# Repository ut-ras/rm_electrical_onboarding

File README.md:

# RoboMaster Electrical Onboarding Project
This repository contains the _onboarding project_ for UT RoboMasters. For the full electrical team onboarding process, see [the main repository's wiki page](https://github.com/ut-ras/robomaster_electrical/wiki/New-Members#onboarding). 
## Overview
This project will take you through the full PCB design process of a boost converter circuit alongside a simple data connection standard. The design process is as follows:

1. Characterization:
   * Defining what the board should do and what problems it needs to solve
2. Schematic creation:
   * Clearly defining circuits and connections without the clutter of physical implementation
   * Running DRC to catch definition errors before they break our board layout
3. Simulation:
   * Simulating the circuits defined in the schematic to verify our intentions
4. Board Layout & Routing:
   * Determining an optimal arrangement for components and routing connections, the physical implementation
   * Running DRC to verify our implementation is manufacturable and repeating anything in steps 2-4 to resolve issues
6. File Export:
   * Generating gerber files that manufacturers can use to produce the board design

This is an **involved process** and will likely take 3-4 hours, but please put some real time and effort in as you will need every skill you develop here.\
Get started by seeing [the wiki](https://github.com/ut-ras/rm_electrical_onboarding/wiki) for this repo.\
**PLEASE** ask questions in the Onboarding Discussion thread on the Discord, someone else likely has the same question!

## Next Steps

TODO: add up-to-date wiring diagram
Once you're done and are looking to see what you'll be applying your skills to, check out [the problem statement presentation](https://github.com/ut-ras/rm_electrical-supercap_v2/blob/main/UT%20Robomasters%20%E2%80%93%20Supercap%20System%20Overview.pptx) for [supercap](https://github.com/ut-ras/rm_electrical-supercap_v2).

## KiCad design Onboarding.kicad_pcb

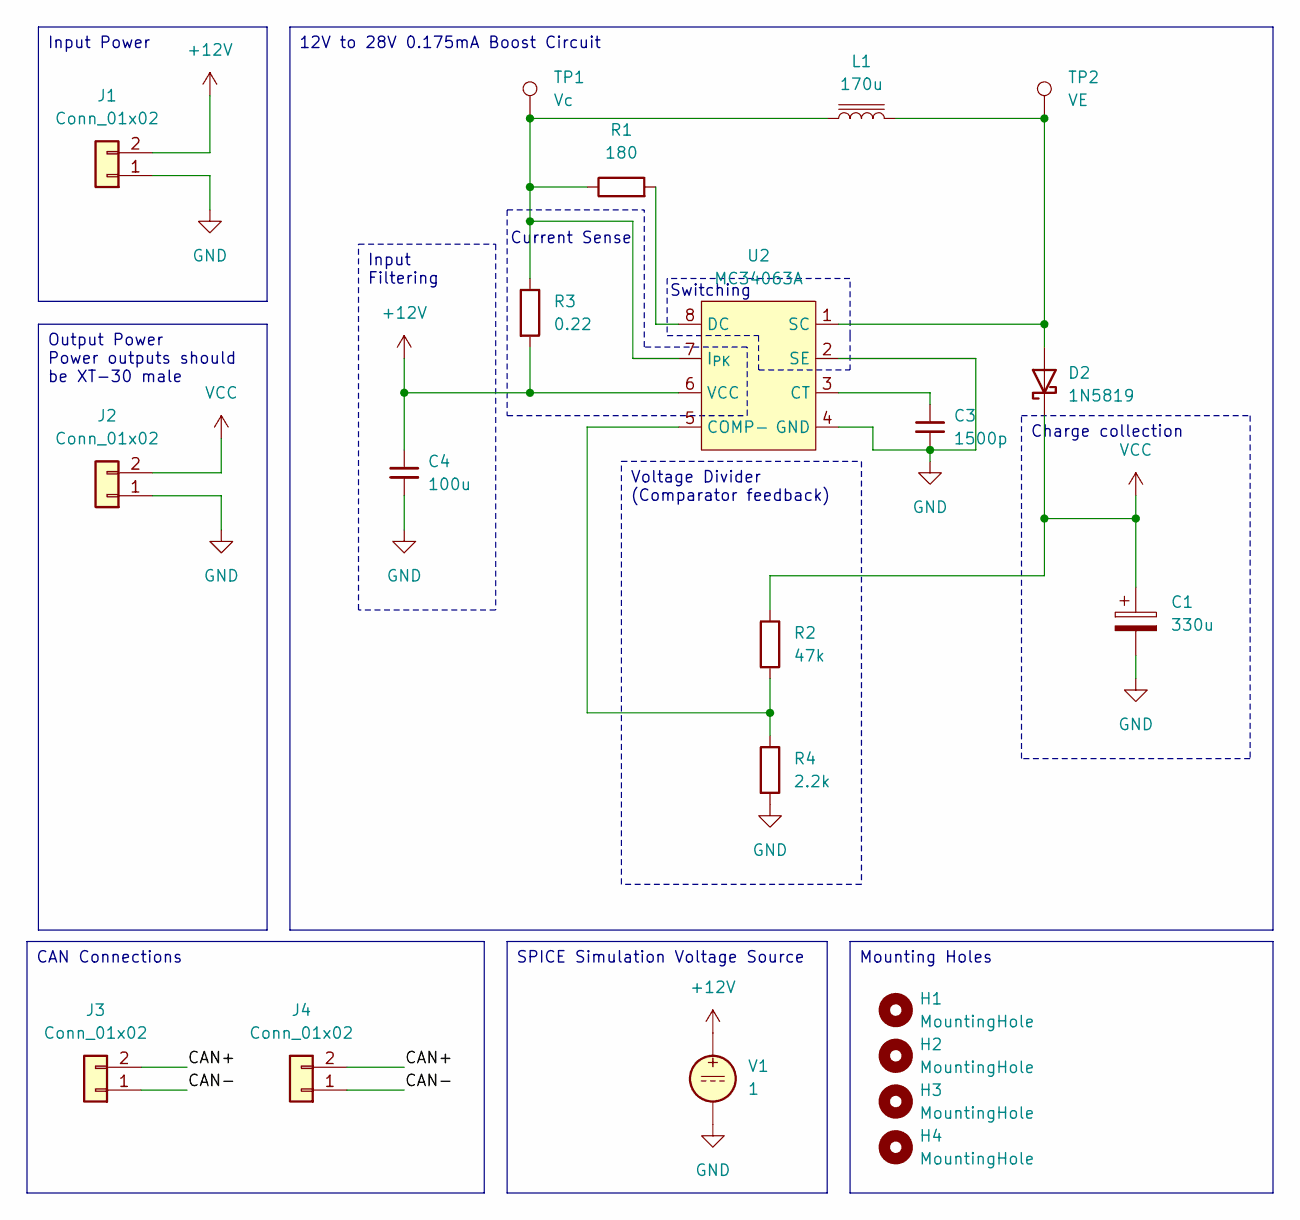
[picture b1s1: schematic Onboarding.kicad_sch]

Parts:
C1: 330u; CP_Radial_D8.0mm_P5.00mm
C3: 1500p; C_0603_1608Metric_Pad1.08x0.95mm_HandSolder
C4: 100u; C_0805_2012Metric
D2: 1N5819; D_SOD-123F
H1, H2, H3, H4: MountingHole; MountingHole_2.2mm_M2
J1: Conn_01x02; AMASS_XT30U-F_1x02_P5.0mm_Vertical
J2: Conn_01x02; AMASS_XT30U-M_1x02_P5.0mm_Vertical
J3, J4: Conn_01x02; JST_GH_BM02B-GHS-TBT_1x02-1MP_P1.25mm_Vertical
L1: 170u; INDM3225X240N
R1: 180; R_0805_2012Metric_Pad1.20x1.40mm_HandSolder
R2: 47k; R_0805_2012Metric_Pad1.20x1.40mm_HandSolder
R3: 0.22; R_0805_2012Metric_Pad1.20x1.40mm_HandSolder
R4: 2.2k; R_0805_2012Metric_Pad1.20x1.40mm_HandSolder
TP1: Vc; TestPoint_Bridge_Pitch2.0mm_Drill0.7mm
TP2: VE; TestPoint_Bridge_Pitch2.0mm_Drill0.7mm
U2: MC34063A; SOIC-8_3.9x4.9mm_P1.27mm; Mouser Part Number 595-MC34063ADR
V1: 1

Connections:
+12V: C4.1, J1.2, R3.2, U2.6 (VCC), V1.1
/CAN+: J3.2, J4.2
/CAN-: J3.1, J4.1
GND: C1.2, C3.2, C4.2, J1.1, J2.1, R4.2, U2.2 (SE), U2.4 (GND), V1.2
unnamed: D2.2 (A), L1.2, TP2.1 (1_1), U2.1 (SC)
unnamed: R2.2, R4.1, U2.5 (COMP-)
unnamed: C3.1, U2.3 (CT)
unnamed: R1.2, U2.8 (DC)
unnamed: L1.1, R1.1, R3.1, TP1.1 (1_1), U2.7 (I_{PK})
VCC: C1.1, D2.1 (K), J2.2, R2.1

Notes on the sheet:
Switching
Current Sense
Input Power
Mounting Holes
Charge collection
CAN Connections
Voltage Divider (Comparator feedback)
12V to 28V 0.175mA Boost Circuit
SPICE Simulation Voltage Source
Output Power Power outputs should be XT-30 male
Input Filtering

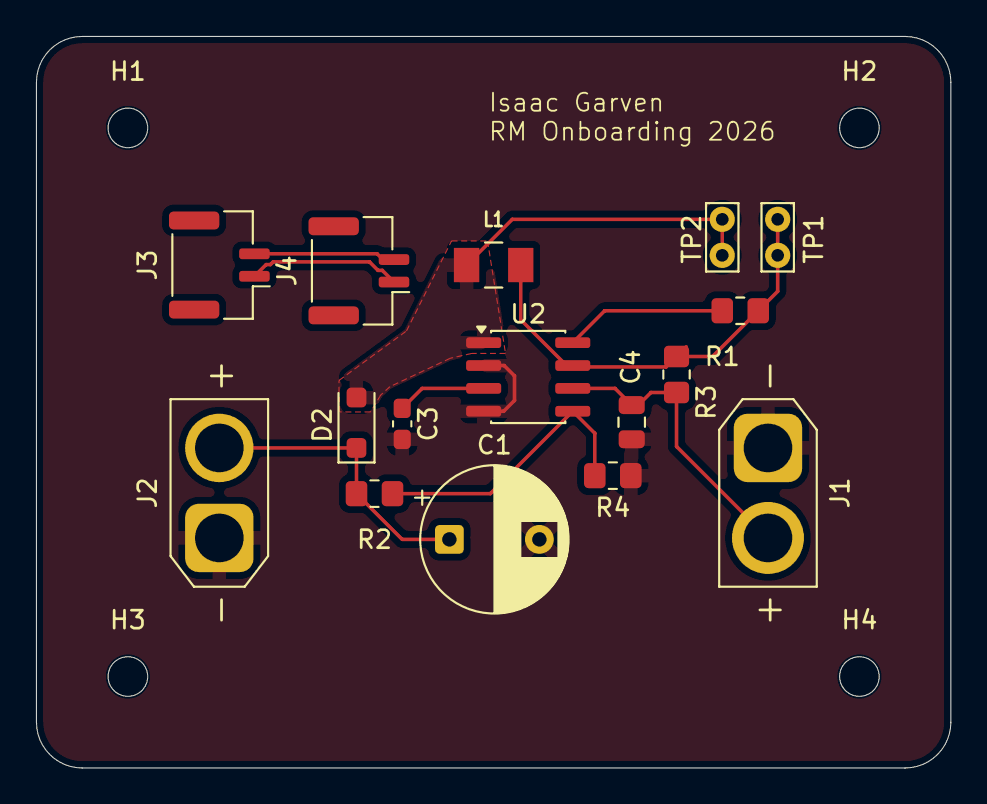
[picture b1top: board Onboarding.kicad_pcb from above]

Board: 2 copper layers, 50.8 x 40.6 mm, 20 parts (0 on the bottom side), 10 nets.

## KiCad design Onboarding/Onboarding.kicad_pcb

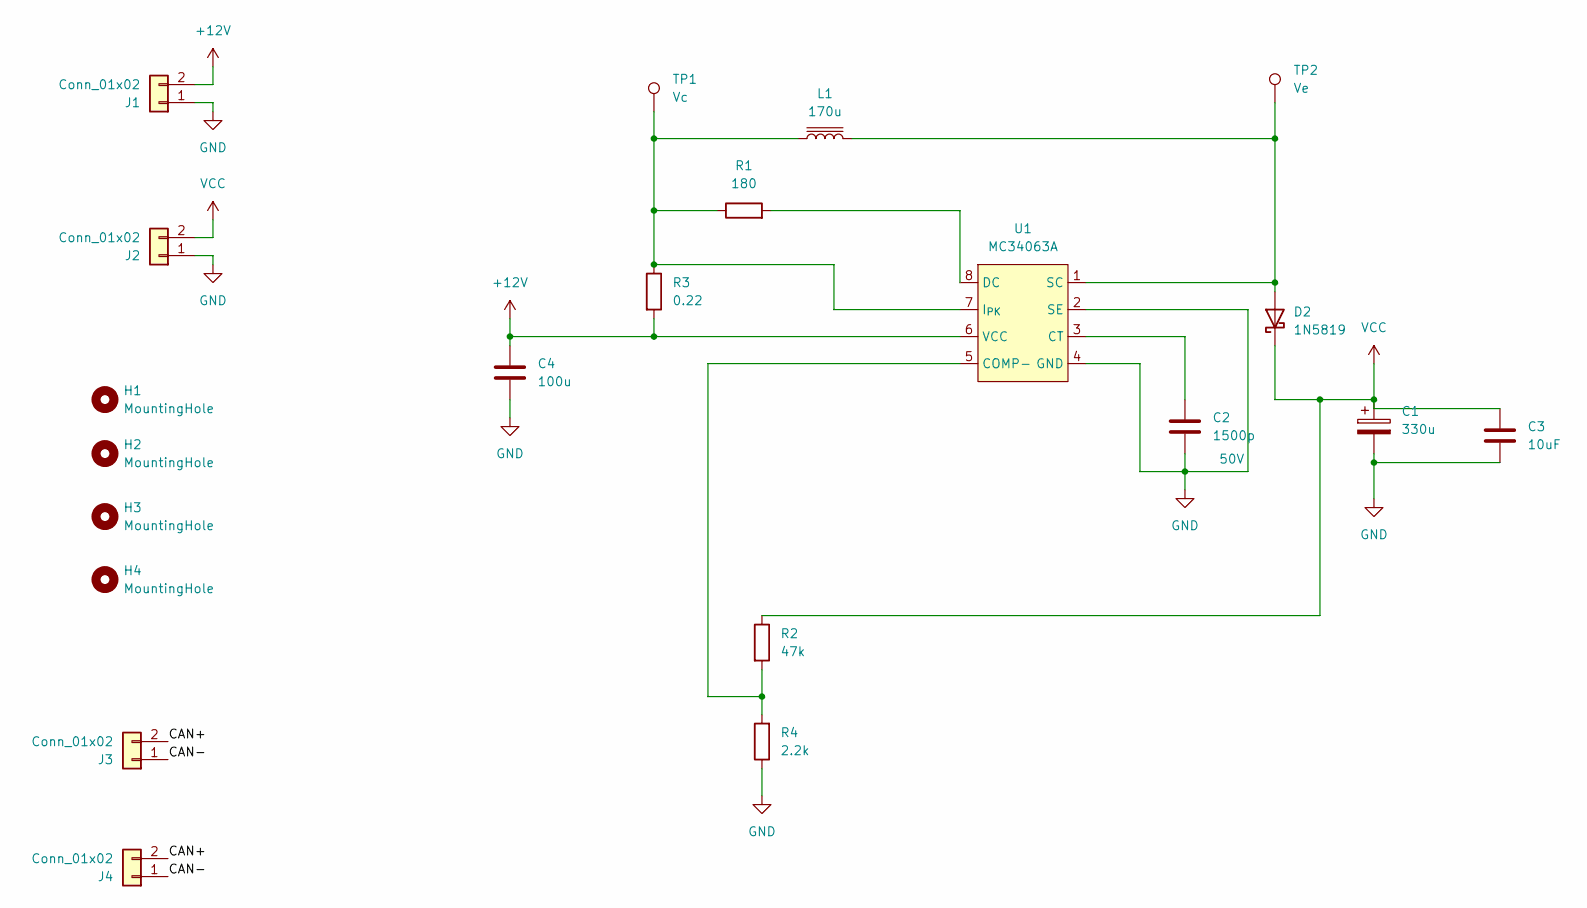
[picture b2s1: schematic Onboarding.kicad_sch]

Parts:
C1: 330u; CP_Radial_D8.0mm_P3.80mm
C2: 1500p; C_0603_1608Metric_Pad1.08x0.95mm_HandSolder; Voltage 50V
C3: 10uF; C_0805_2012Metric
C4: 100u; C_0805_2012Metric
D2: 1N5819; D_SOD-123F
H1, H2, H3, H4: MountingHole; MountingHole_2.2mm_M2
J1: Conn_01x02; AMASS_XT30U-F_1x02_P5.0mm_Vertical
J2: Conn_01x02; AMASS_XT30U-M_1x02_P5.0mm_Vertical
J3, J4: Conn_01x02; JST_GH_BM02B-GHS-TBT_1x02-1MP_P1.25mm_Vertical
L1: 170u; SPT30L174MLD
R1: 180; R_0805_2012Metric_Pad1.20x1.40mm_HandSolder
R2: 47k; R_0603_1608Metric_Pad0.98x0.95mm_HandSolder
R3: 0.22; R_0603_1608Metric_Pad0.98x0.95mm_HandSolder
R4: 2.2k; R_0603_1608Metric_Pad0.98x0.95mm_HandSolder
TP1: Vc; TestPoint_Bridge_Pitch2.0mm_Drill0.7mm
TP2: Ve; TestPoint_Bridge_Pitch2.0mm_Drill0.7mm
U1: MC34063A; SOIC-8_3.9x4.9mm_P1.27mm; Mouser Part Number 595-MC34063ADR

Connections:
+12V: C4.1, J1.2, R3.2, U1.6 (VCC)
/CAN+: J3.2, J4.2
/CAN-: J3.1, J4.1
GND: C1.2, C2.2, C3.1, C4.2, J1.1, J2.1, R4.1, U1.2 (SE), U1.4 (GND)
unnamed: D2.2 (A), L1.2, TP2.1 (1_1), U1.1 (SC)
unnamed: R2.2, R4.2, U1.5 (COMP-)
unnamed: C2.1, U1.3 (CT)
unnamed: R1.2, U1.8 (DC)
unnamed: L1.1, R1.1, R3.1, TP1.1 (1_1), U1.7 (I_{PK})
VCC: C1.1, C3.2, D2.1 (K), J2.2, R2.1

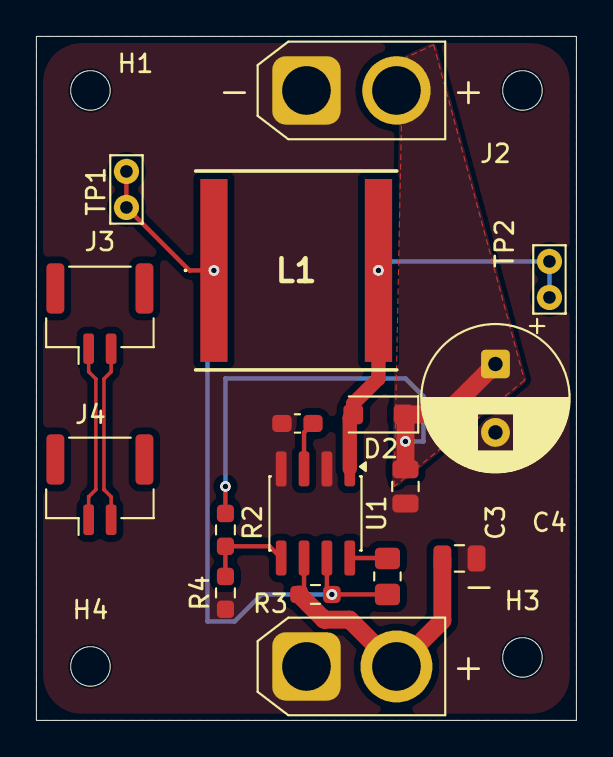
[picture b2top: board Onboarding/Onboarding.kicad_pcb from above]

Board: 2 copper layers, 30.0 x 38.0 mm, 21 parts (0 on the bottom side), 10 nets.

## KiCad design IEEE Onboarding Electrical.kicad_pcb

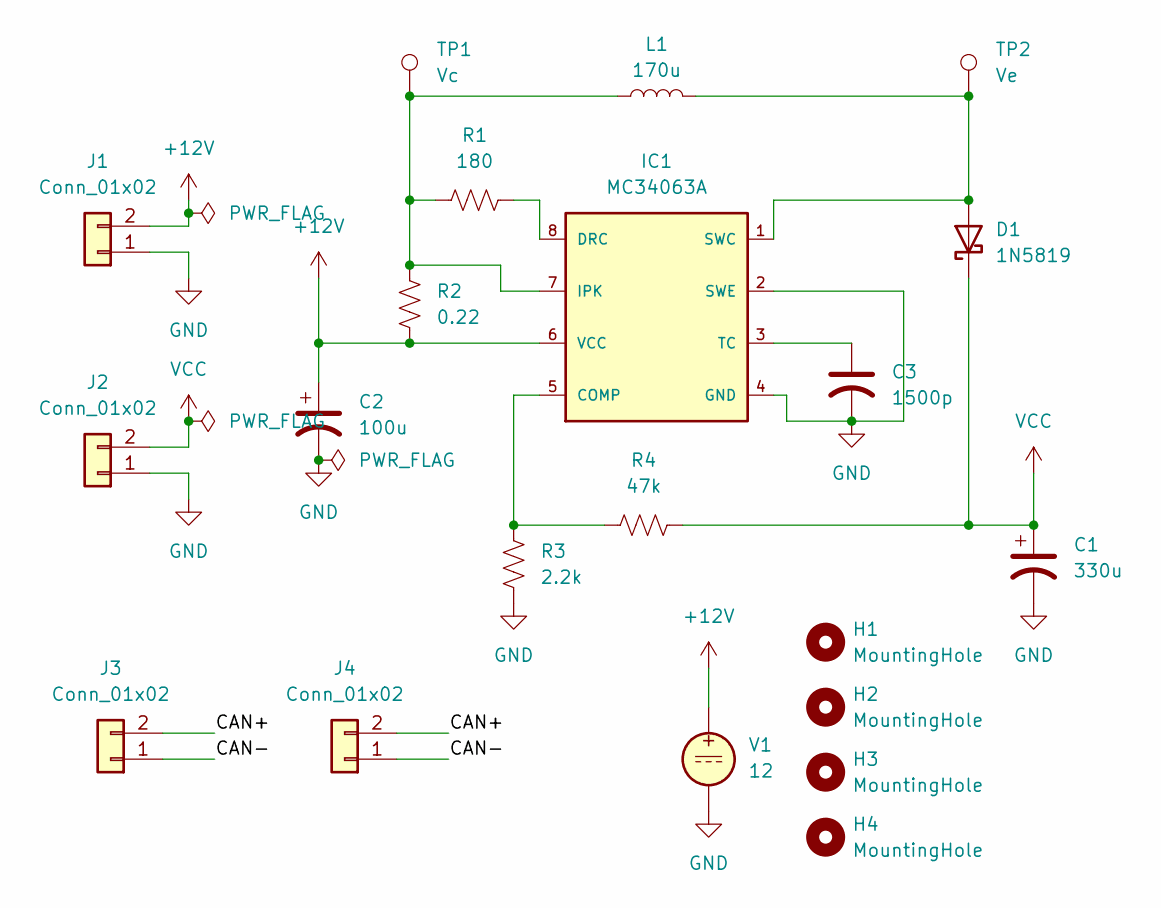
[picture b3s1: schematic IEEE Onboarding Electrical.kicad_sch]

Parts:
C1: 330u; CP_Radial_D8.0mm_P5.00mm
C2: 100u; C_0805_2012Metric
C3: 1500p; C_0603_1608Metric_Pad1.08x0.95mm_HandSolder
D1: 1N5819; D_SOD-123F
H1, H2, H3, H4: MountingHole; MountingHole_2.2mm_M2
IC1: MC34063A; SOIC-8_3.9x4.9mm_P1.27mm
J1: Conn_01x02; AMASS_XT30U-F_1x02_P5.0mm_Vertical
J2: Conn_01x02; AMASS_XT30U-M_1x02_P5.0mm_Vertical
J3, J4: Conn_01x02; JST_PH_B2B-PH-K_1x02_P2.00mm_Vertical
L1: 170u; PE53828SNLT
R1: 180; R_0805_2012Metric_Pad1.20x1.40mm_HandSolder
R2: 0.22; R_0603_1608Metric_Pad0.98x0.95mm_HandSolder
R3: 2.2k; R_0603_1608Metric_Pad0.98x0.95mm_HandSolder
R4: 47k; R_0603_1608Metric_Pad0.98x0.95mm_HandSolder
TP1: Vc; TestPoint_Bridge_Pitch2.0mm_Drill0.7mm
TP2: Ve; TestPoint_Bridge_Pitch2.0mm_Drill0.7mm
V1: 12

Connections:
+12V: C2.1, IC1.6 (VCC), J1.2, R2.2, V1.1
/CAN+: J3.2, J4.2
/CAN-: J3.1, J4.1
GND: C1.2, C2.2, C3.2, IC1.2 (SWE), IC1.4 (GND), J1.1, J2.1, R3.2, V1.2
unnamed: D1.2 (A), IC1.1 (SWC), L1.2, TP2.1 (1_1)
unnamed: IC1.5 (COMP), R3.1, R4.2
unnamed: IC1.8 (DRC), R1.2
unnamed: IC1.7 (IPK), L1.1, R1.1, R2.1, TP1.1 (1_1)
unnamed: C3.1, IC1.3 (TC)
VCC: C1.1, D1.1 (K), J2.2, R4.1

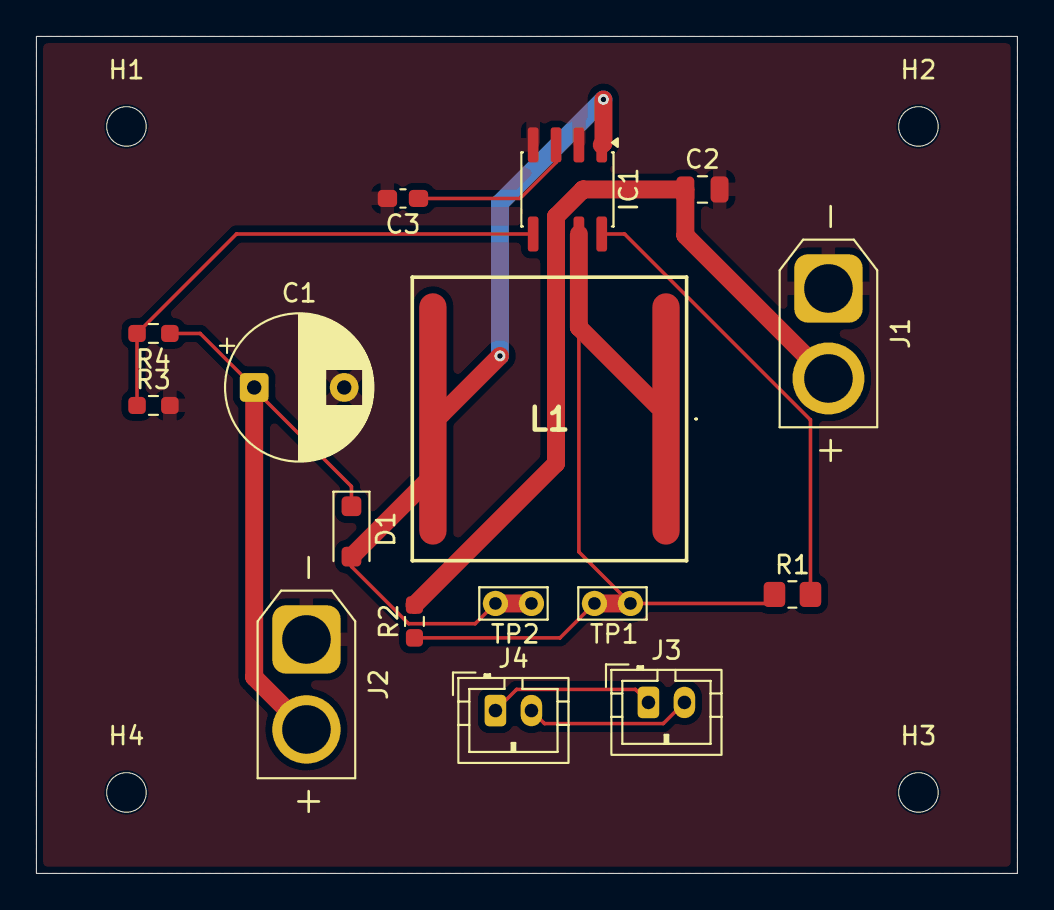
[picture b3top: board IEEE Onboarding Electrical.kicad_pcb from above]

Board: 2 copper layers, 54.5 x 46.5 mm, 20 parts (0 on the bottom side), 10 nets.

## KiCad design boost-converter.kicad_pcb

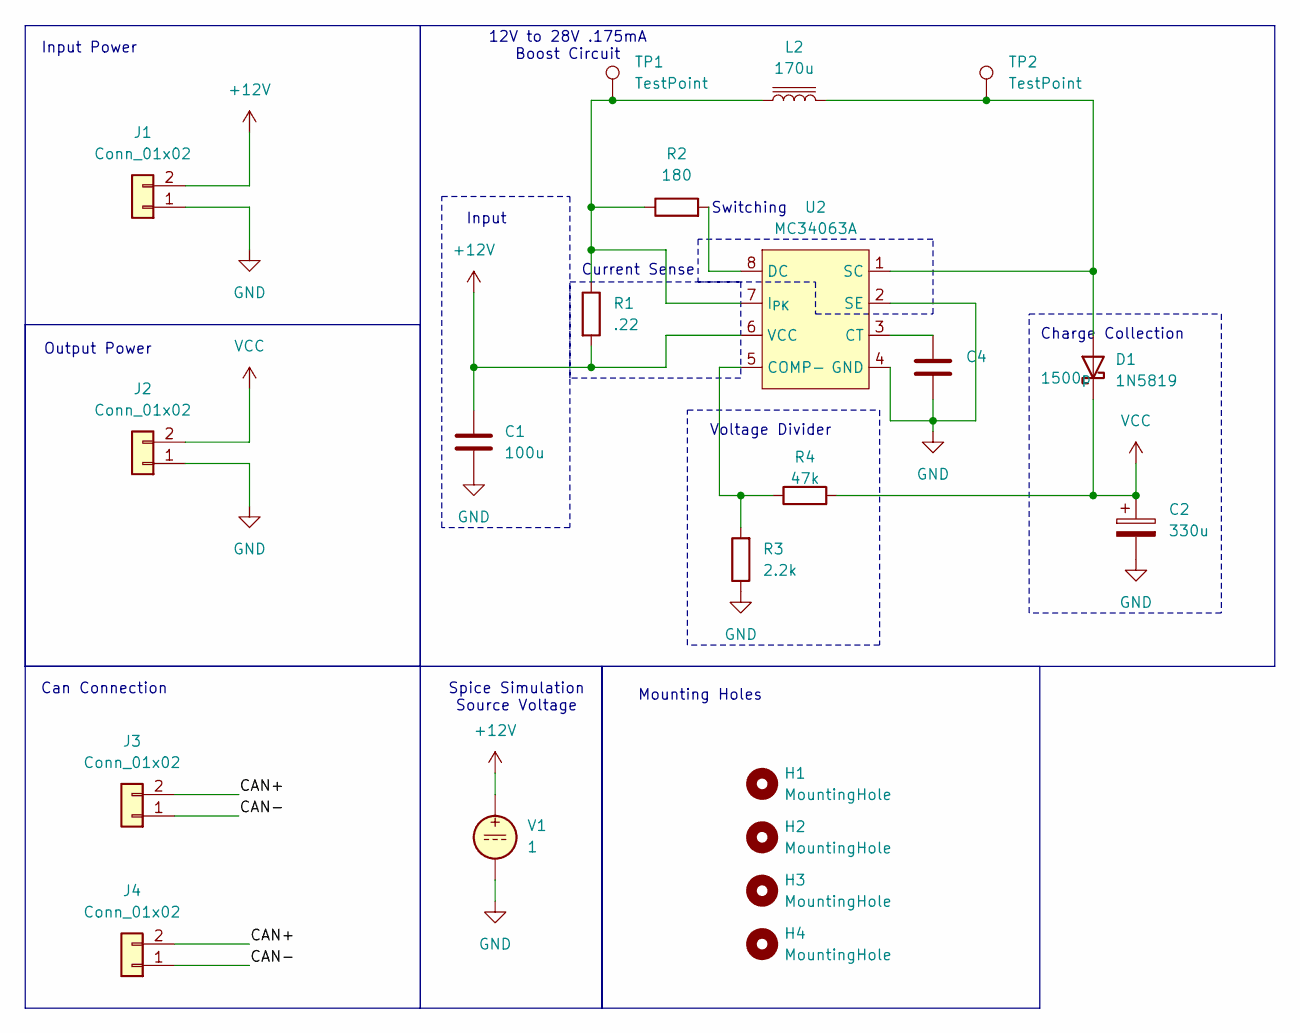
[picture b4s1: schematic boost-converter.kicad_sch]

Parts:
C1: 100u; CP_Radial_D8.0mm_P5.00mm
C2: 330u; C_0603_1608Metric_Pad1.08x0.95mm_HandSolder
C4: 1500p; C_0805_2012Metric
D1: 1N5819; D_SOD-123F
H1, H2, H3, H4: MountingHole; MountingHole_2.2mm_M2
J1: Conn_01x02; AMASS_XT30U-F_1x02_P5.0mm_Vertical
J2: Conn_01x02; AMASS_XT30U-M_1x02_P5.0mm_Vertical
J3, J4: Conn_01x02; JST_GH_BM02B-GHS-TBT_1x02-1MP_P1.25mm_Vertical
L2: 170u; SRR1210181M
R1: .22; R_0603_1608Metric_Pad0.98x0.95mm_HandSolder
R2: 180; R_0805_2012Metric_Pad1.20x1.40mm_HandSolder
R3: 2.2k; R_0603_1608Metric_Pad0.98x0.95mm_HandSolder
R4: 47k; R_0603_1608Metric_Pad0.98x0.95mm_HandSolder
TP1, TP2: TestPoint; TestPoint_Bridge_Pitch2.0mm_Drill0.7mm
U2: MC34063A; SOIC-8_3.9x4.9mm_P1.27mm; Mouser Part Number 595-MC34063ADR
V1: 1

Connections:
+12V: C1.1, J1.2, R1.2, U2.6 (VCC), V1.1
/CAN+: J3.2, J4.2
/CAN-: J3.1, J4.1
GND: C1.2, C2.2, C4.2, J1.1, J2.1, R3.1, U2.2 (SE), U2.4 (GND), V1.2
unnamed: D1.2 (A), L2.2, TP2.1, U2.1 (SC)
unnamed: R3.2, R4.1, U2.5 (COMP-)
unnamed: C4.1, U2.3 (CT)
unnamed: R2.2, U2.8 (DC)
unnamed: L2.1, R1.1, R2.1, TP1.1, U2.7 (I_{PK})
VCC: C2.1, D1.1 (K), J2.2, R4.2

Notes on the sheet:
Spice Simulation Source Voltage
Charge Collection
Output Power
12V to 28V .175mA Boost Circuit
Can Connection
Input Power
Mounting Holes
Switching
Current Sense
Input
Voltage Divider

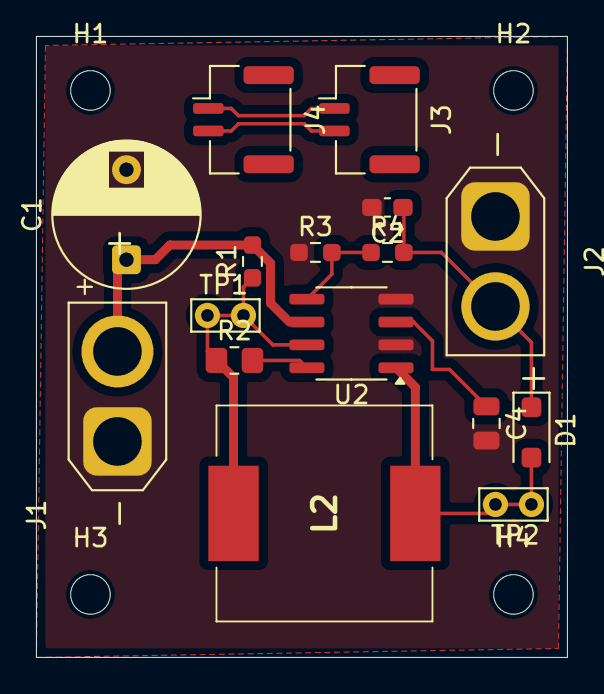
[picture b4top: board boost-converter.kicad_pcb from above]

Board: 2 copper layers, 29.5 x 34.5 mm, 20 parts (0 on the bottom side), 10 nets.

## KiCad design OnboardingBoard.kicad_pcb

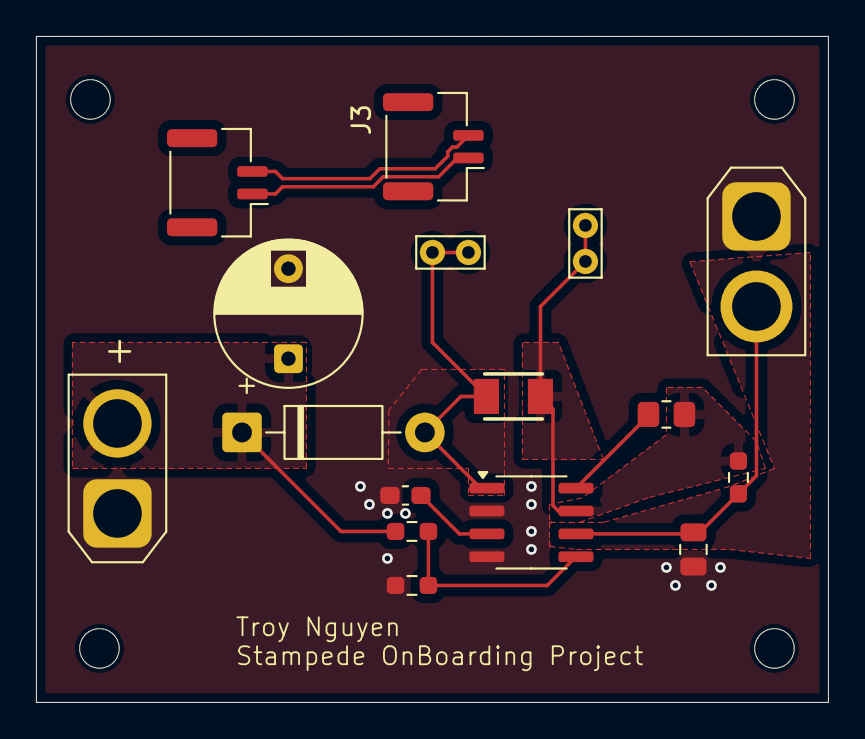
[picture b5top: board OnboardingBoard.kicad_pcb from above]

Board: 2 copper layers, 44.0 x 37.0 mm, 20 parts (0 on the bottom side), 10 nets.

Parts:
C1: 330u; CP_Radial_D8.0mm_P5.00mm
C2: 1500p; C_0603_1608Metric_Pad1.08x0.95mm_HandSolder
C4: 100u; C_0805_2012Metric
D1: 1N5819; D_DO-41_SOD81_P10.16mm_Horizontal
H1, H2, H3, H4: MountingHole; MountingHole_2.2mm_M2
J1: Conn_01x02; AMASS_XT30U-F_1x02_P5.0mm_Vertical
J2: Conn_01x02; AMASS_XT30U-M_1x02_P5.0mm_Vertical
J3, J4: Conn_01x02; JST_GH_BM02B-GHS-TBT_1x02-1MP_P1.25mm_Vertical
L1: 170u; INDM3225X240N
R2: 47k; R_0603_1608Metric_Pad0.98x0.95mm_HandSolder
R3: 180; R_0805_2012Metric_Pad1.20x1.40mm_HandSolder
R4: 2.2k; R_0603_1608Metric_Pad0.98x0.95mm_HandSolder
R5: 0.22; R_0603_1608Metric_Pad0.98x0.95mm_HandSolder
TP2: V_{C}; TestPoint_Bridge_Pitch2.0mm_Drill0.7mm
TP3: V_{E}; TestPoint_Bridge_Pitch2.0mm_Drill0.7mm
U2: MC34063A; SOIC-8_3.9x4.9mm_P1.27mm

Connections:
+12V: C4.1, J1.2, R5.2, U2.6 (VCC)
/CAN+: J3.2, J4.2
/CAN-: J3.1, J4.1
GND: C1.2, C2.2, C4.2, J1.1, J2.1, R4.2, U2.2 (SE), U2.4 (GND)
unnamed: D1.2 (A), L1.2, TP3.1, U2.1 (SC)
unnamed: R2.2, R4.1, U2.5 (COMP-)
unnamed: C2.1, U2.3 (CT)
unnamed: R3.2, U2.8 (DC)
unnamed: L1.1, R3.1, R5.1, TP2.1, U2.7 (I_{PK})
VCC: C1.1, D1.1 (K), J2.2, R2.1

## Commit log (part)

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2025-09-01 Rennamed project, added KiCad_Library submodule
2025-09-04 Created example branch, started annotations
2025-09-07 finishing example schematic
2025-09-08 Finished example schematic and component layout
2025-09-08 Finished onboarding example layout
2025-09-08 Fixed mountinghole exclusion from simulation
2025-09-10 Added SPICE models for diode and controller
2025-09-12 Test Commit
2025-09-20 bruh
2025-09-21 Finish Schematic
2025-09-21 Merged in supercap stuff
2025-09-22 Update PCB
2025-09-25 Finish PCB
2025-09-25 Added jlcpcb extension exports, updated Kicad library
2025-09-26 Finish Onboarding
2025-09-26 timothy-yeap onboarding
2025-09-26 started on my onboarding
2025-09-27 Troy Nguyen OnBoarding Project
2025-09-27 Update PCB Board
2025-09-28 Fully designed PCB and schematic
2025-09-28 Haici onboarding
2025-09-28 UpdatePCB
2025-09-28 Final PCB Update
2025-09-28 Onboarding done, waiting review
2025-09-28 Updated Schematic
2025-10-01 added new inductor, vias, and pours
2025-10-05 Finished PCB
2025-10-05 boe jiden
2025-10-09 tonald drump
2025-10-10 first
2025-10-12 Completed onboarding
2025-10-12 made pcb tighter
2025-10-12 onboarding project
2025-10-15 Saaketh Manepalli Onboarding
2026-01-28 Updated Schematics
2026-01-28 PCB Finished
2026-02-01 Nan_Jiang Nan's onboarding project in Robomaster Electrical
2026-02-01 Nan_Jiang
2026-02-01 Nan_Jiang njiang2005@gmail.com
2026-02-01 commit ethanchu
2026-02-07 Nan_Jiang v2
2026-02-07 Ethan_Chu
2026-02-08 update files
2026-02-20 Onboarding
2026-02-20 filleted corners
2026-02-23 Yippee
2026-03-07 updated onboarding
2026-03-07 fixed onboarding
2026-03-07 fixed 90 degree angle
2026-03-12 RoboMaster Onboarding
2026-03-23 Robomaster Onboarding v2
